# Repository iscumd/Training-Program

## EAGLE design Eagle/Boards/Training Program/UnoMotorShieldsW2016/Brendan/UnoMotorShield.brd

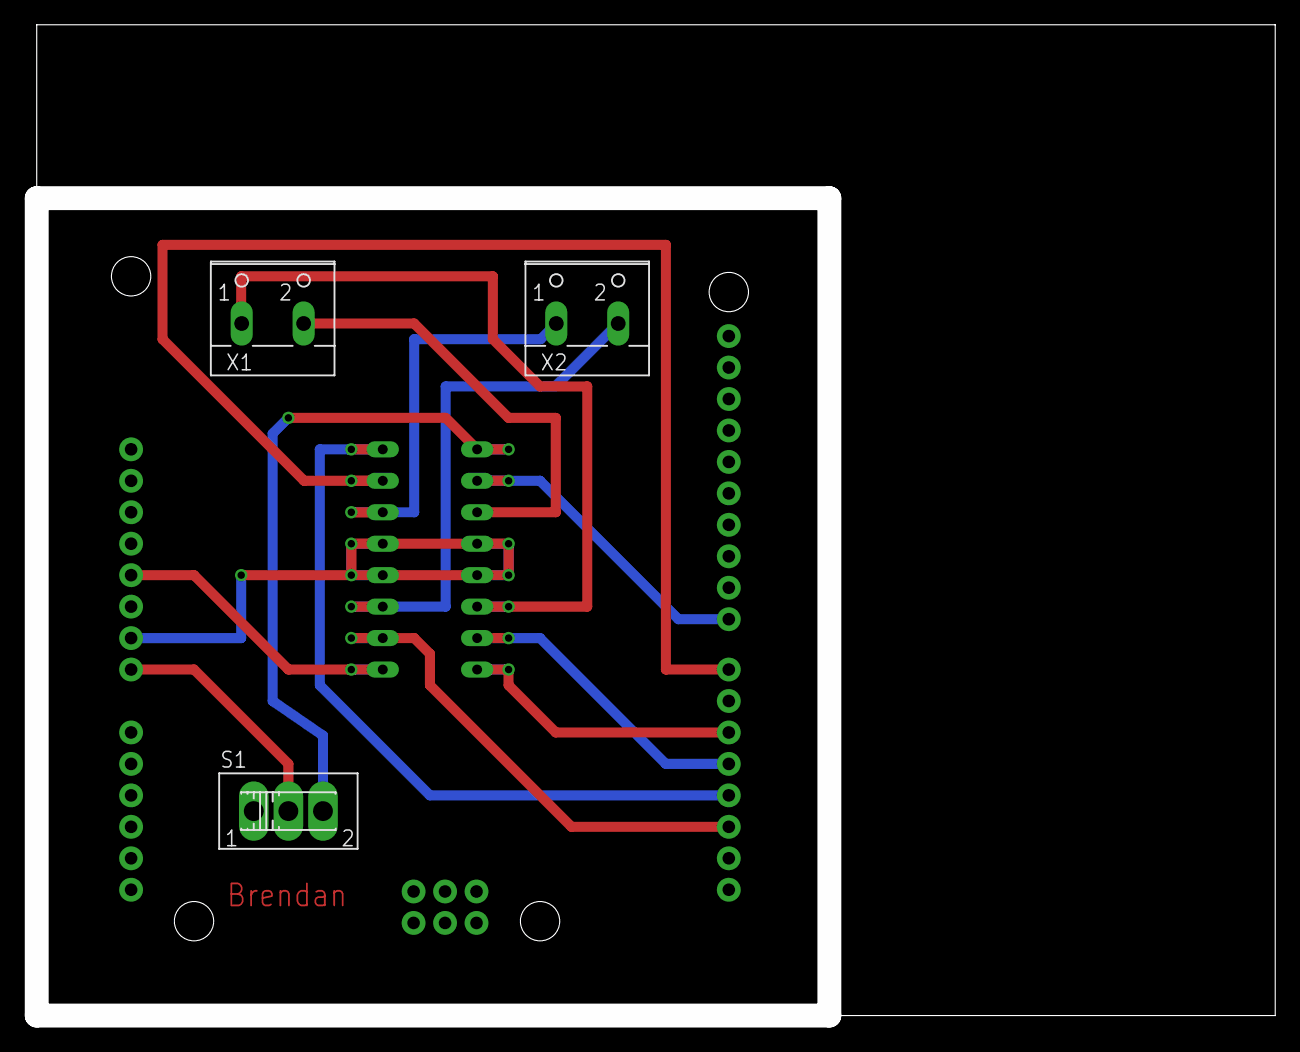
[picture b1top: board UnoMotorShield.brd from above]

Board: 2 copper layers, 100.0 x 80.0 mm, 5 parts (0 on the bottom side), 14 nets.

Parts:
J1: ARDUINO_UNO_R3; ARDUINO_R3
S1: SLIDE_SWITCH
U$1: MOTOR_DRIVERDIP16; DIP16
X1, X2: 2PIN-SCREW-TERMINAL

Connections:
unnamed: U$1.P3, X1.1
unnamed: U$1.P6, X1.2
unnamed: U$1.P11, X2.1
unnamed: U$1.P14, X2.2
unnamed: J1.5V, U$1.P16
unnamed: J1.GND@2, U$1.P4, U$1.P5, U$1.P12, U$1.P13
unnamed: J1.VIN, S1.2
unnamed: S1.3, U$1.P8
unnamed: J1.D2, U$1.P15
unnamed: J1.D3, U$1.P9
unnamed: J1.D4, U$1.P2
unnamed: J1.D5, U$1.P1
unnamed: J1.D7, U$1.P10
unnamed: J1.D8, U$1.P7

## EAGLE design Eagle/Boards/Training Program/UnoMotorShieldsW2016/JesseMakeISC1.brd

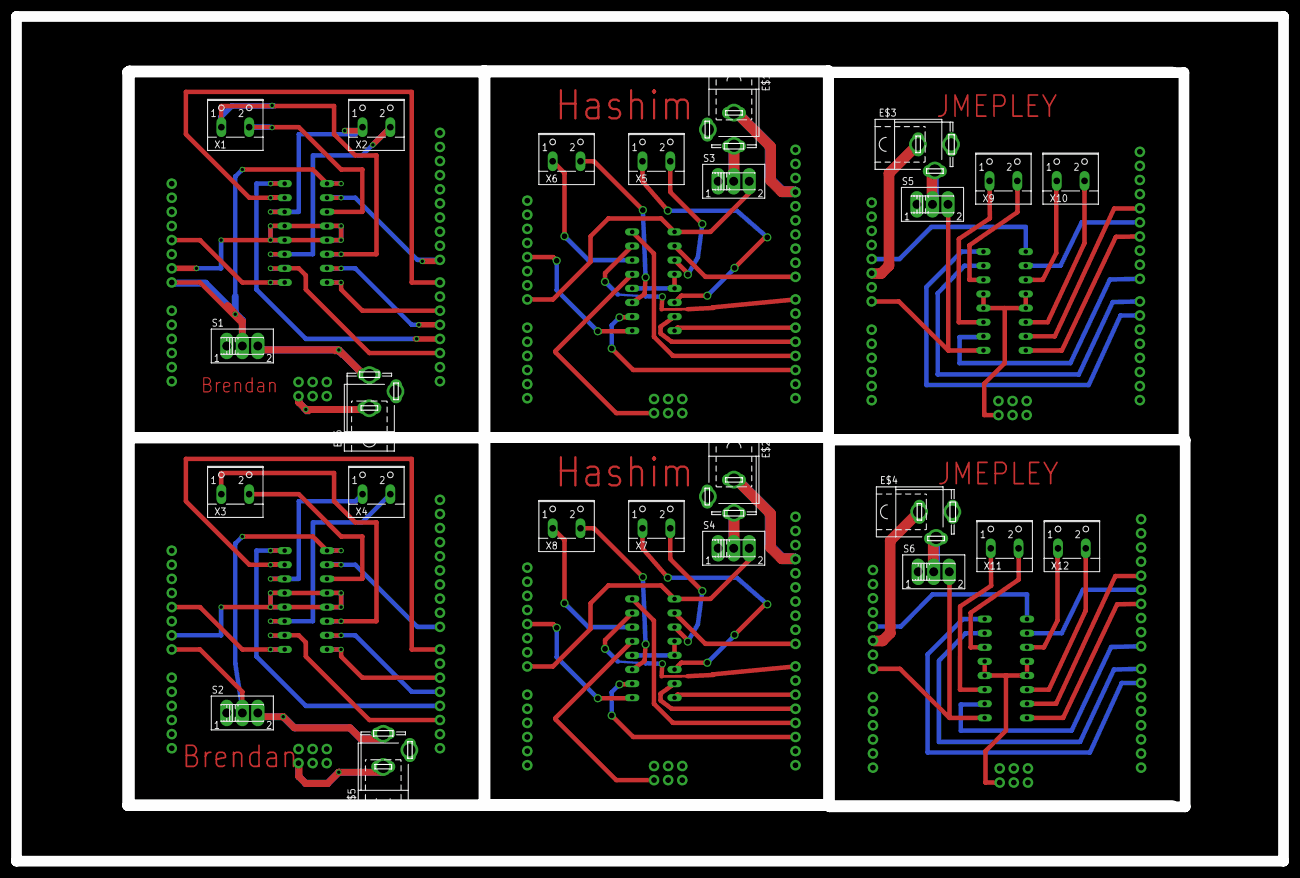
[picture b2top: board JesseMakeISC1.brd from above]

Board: 2 copper layers, 228.0 x 152.0 mm, 36 parts (0 on the bottom side), 80 nets.

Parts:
E$1, E$2, E$3, E$4, E$5, E$6: 5.5-2.5-BARRELCONNECTOR
J1, J2, J3, J4, J5, J6: ARDUINO_UNO_R3; ARDUINO_R3
S1, S2, S3, S4, S5, S6: SLIDE_SWITCH
U$1, U$2, U$3, U$4, U$5, U$6: MOTOR_DRIVERDIP16; DIP16
X1, X2, X3, X4, X5, X6, X7, X8, X9, X10, X11, X12: 2PIN-SCREW-TERMINAL

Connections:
1A: J5.D7, U$5.P2
1A1: J6.D7, U$6.P2
2A: J5.D8, U$5.P7
2A1: J6.D8, U$6.P7
3A: J5.D13, U$5.P10
3A1: J6.D13, U$6.P10
4A: J5.D12, U$5.P15
4A1: J6.D12, U$6.P15
EN1: J5.D6, U$5.P1
EN2: J5.D11, U$5.P9
EN3: J6.D11, U$6.P9
EN4: J6.D6, U$6.P1
GND: U$3.P4, U$3.P5, U$3.P13
GND1: U$4.P4, U$4.P5, U$4.P13
GND2: J5.GND@4, U$5.P4, U$5.P5, U$5.P12, U$5.P13
GND3: J6.GND@4, U$6.P4, U$6.P5, U$6.P12, U$6.P13
unnamed: U$1.P3, X1.1
unnamed: U$1.P6, X1.2
unnamed: U$1.P11, X2.1
unnamed: U$1.P14, X2.2
unnamed: J1.5V, U$1.P16
unnamed: J1.GND@2, U$1.P4, U$1.P5, U$1.P12, U$1.P13
unnamed: J1.VIN, S1.2, U$1.P8
unnamed: J1.D2, U$1.P15
unnamed: J1.D3, U$1.P9
unnamed: J1.D4, U$1.P2
unnamed: J1.D5, U$1.P1
unnamed: J1.D7, U$1.P10
unnamed: J1.D8, U$1.P7
unnamed: U$2.P3, X3.1
unnamed: U$2.P6, X3.2
unnamed: U$2.P11, X4.1
unnamed: U$2.P14, X4.2
unnamed: J2.5V, U$2.P16
unnamed: J2.GND@2, U$2.P4, U$2.P5, U$2.P12, U$2.P13
unnamed: J2.VIN, S2.2
unnamed: J2.D2, U$2.P15
unnamed: J2.D3, U$2.P9
unnamed: J2.D4, U$2.P2
unnamed: J2.D5, U$2.P1
unnamed: J2.D7, U$2.P10
unnamed: J2.D8, U$2.P7
unnamed: U$3.P3, X5.1
unnamed: U$3.P6, X5.2
unnamed: U$3.P11, X6.1
unnamed: U$3.P14, X6.2
unnamed: J3.5V, U$3.P16
unnamed: J3.GND@4, U$3.P12
unnamed: J3.VIN, S3.3, U$3.P8
unnamed: J3.D2, U$3.P15
unnamed: J3.D3, U$3.P9
unnamed: J3.D8, U$3.P7
unnamed: J3.D7, U$3.P10
unnamed: J3.D4, U$3.P2
unnamed: J3.D5, U$3.P1
unnamed: U$4.P3, X7.1
unnamed: U$4.P6, X7.2
unnamed: U$4.P11, X8.1
unnamed: U$4.P14, X8.2
unnamed: J4.5V, U$4.P16
unnamed: J4.GND@4, U$4.P12
unnamed: J4.VIN, S4.3, U$4.P8
unnamed: J4.D2, U$4.P15
unnamed: J4.D3, U$4.P9
unnamed: J4.D8, U$4.P7
unnamed: J4.D7, U$4.P10
unnamed: J4.D4, U$4.P2
unnamed: J4.D5, U$4.P1
unnamed: U$5.P6, X9.1
unnamed: U$5.P3, X9.2
unnamed: U$5.P14, X10.1
unnamed: U$5.P11, X10.2
unnamed: J5.5V, U$5.P16
unnamed: J5.VIN, S5.3, U$5.P8
unnamed: U$6.P6, X11.1
unnamed: U$6.P3, X11.2
unnamed: U$6.P14, X12.1
unnamed: U$6.P11, X12.2
unnamed: J6.5V, U$6.P16
unnamed: J6.VIN, S6.3, U$6.P8

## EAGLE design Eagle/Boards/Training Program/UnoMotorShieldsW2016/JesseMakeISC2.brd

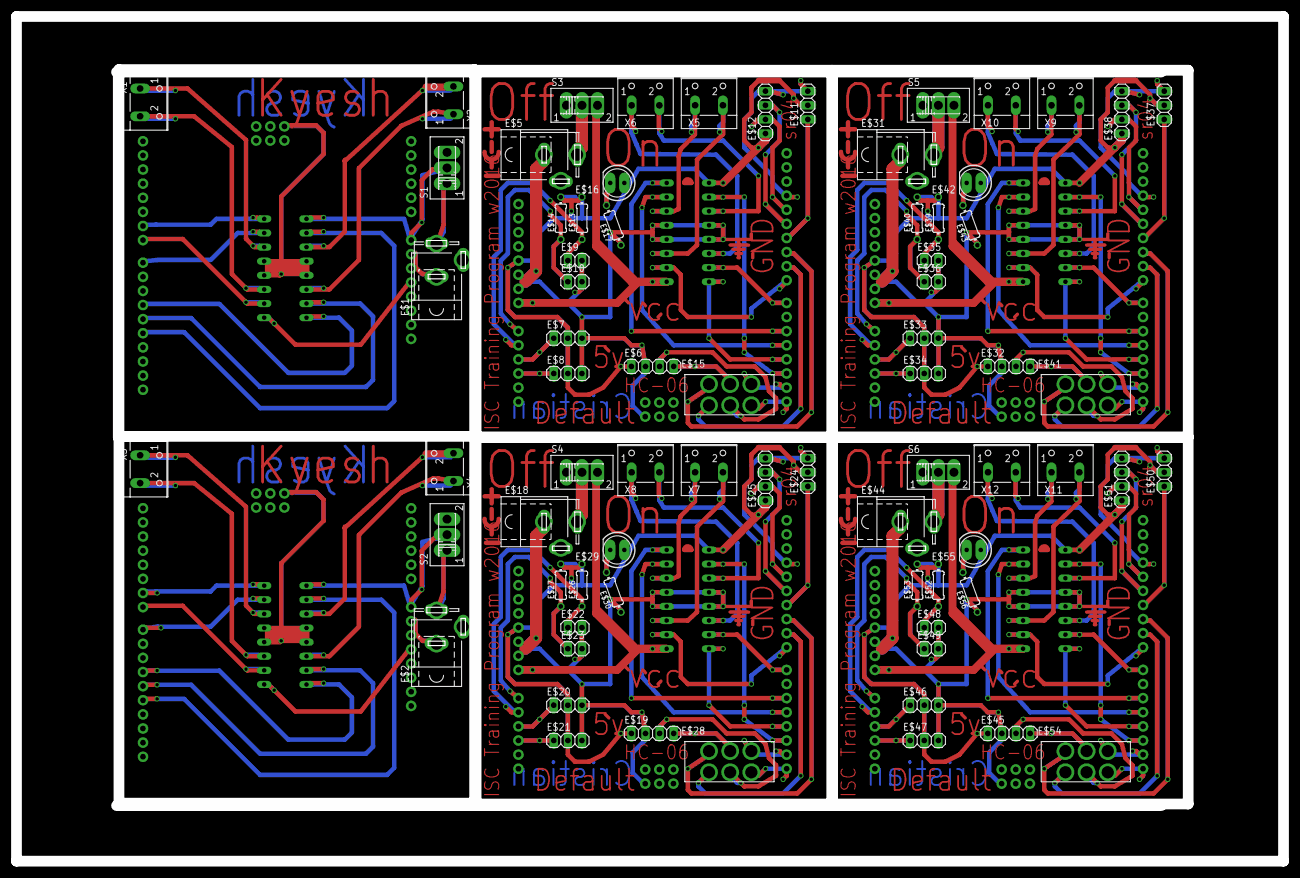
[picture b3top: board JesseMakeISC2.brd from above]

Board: 2 copper layers, 228.0 x 152.0 mm, 84 parts (0 on the bottom side), 78 nets.

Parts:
E$1, E$2, E$5, E$18, E$31, E$44: 5.5-2.5-BARRELCONNECTOR
E$3, E$4: ARDUINO_R3
E$6, E$12, E$19, E$25, E$32, E$38, E$45, E$51: 1X04
E$7, E$8, E$11, E$20, E$21, E$24, E$33, E$34, E$37, E$46, E$47, E$50: 1X03
E$9, E$10, E$22, E$23, E$35, E$36, E$48, E$49: 1X02
E$13, E$14, E$17, E$26, E$27, E$30, E$39, E$40, E$43, E$52, E$53, E$56: 0204/7
E$15, E$28, E$41, E$54: DUAL_SLIDE_SWITCH
E$16, E$29, E$42, E$55: LED5MM
ENABLE, ENABLE1: MOTOR_DRIVERDIP16; DIP16
J1, J2, J3, J4: ARDUINO_UNO_R3; ARDUINO_R3
S1, S2, S3, S4, S5, S6: SLIDE_SWITCH
U$1, U$2, U$3, U$4: MOTOR_DRIVERDIP16; DIP16
X1, X2, X3, X4, X5, X6, X7, X8, X9, X10, X11, X12: 2PIN-SCREW-TERMINAL

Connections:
GND: ENABLE.P4, ENABLE.P5, ENABLE.P12
GND1: ENABLE1.P4, ENABLE1.P5, ENABLE1.P12
unnamed: ENABLE.P3, X2.1
unnamed: ENABLE.P8, S1.2
unnamed: ENABLE.P11, X1.1
unnamed: ENABLE.P14, X1.2
unnamed: ENABLE1.P3, X4.1
unnamed: ENABLE1.P8, S2.2
unnamed: ENABLE1.P11, X3.1
unnamed: ENABLE1.P14, X3.2
unnamed: U$1.P6, X5.2
unnamed: U$1.P14, X6.2
unnamed: U$1.P11, X6.1
unnamed: E$6.1, E$8.2, E$12.1, E$13.2, E$14.2, J1.5V, U$1.P16
unnamed: E$6.2, E$8.3, E$9.2, U$1.P4, U$1.P5, U$1.P12, U$1.P13
unnamed: J1.VIN, S3.3, U$1.P8
unnamed: J1.D2, U$1.P15
unnamed: J1.D3, U$1.P9
unnamed: J1.D7, U$1.P10
unnamed: J1.D5, U$1.P1
unnamed: J1.D4, U$1.P2
unnamed: U$1.P3, X5.1
unnamed: J1.D8, U$1.P7
unnamed: U$2.P6, X7.2
unnamed: U$2.P14, X8.2
unnamed: U$2.P11, X8.1
unnamed: E$19.1, E$21.2, E$25.1, E$26.2, E$27.2, J2.5V, U$2.P16
unnamed: E$19.2, E$21.3, E$22.2, U$2.P4, U$2.P5, U$2.P12, U$2.P13
unnamed: J2.VIN, S4.3, U$2.P8
unnamed: J2.D2, U$2.P15
unnamed: J2.D3, U$2.P9
unnamed: J2.D7, U$2.P10
unnamed: J2.D5, U$2.P1
unnamed: J2.D4, U$2.P2
unnamed: U$2.P3, X7.1
unnamed: J2.D8, U$2.P7
unnamed: U$3.P6, X9.2
unnamed: U$3.P14, X10.2
unnamed: U$3.P11, X10.1
unnamed: E$32.1, E$34.2, E$38.1, E$39.2, E$40.2, J3.5V, U$3.P16
unnamed: E$32.2, E$34.3, E$35.2, U$3.P4, U$3.P5, U$3.P12, U$3.P13
unnamed: J3.VIN, S5.3, U$3.P8
unnamed: J3.D2, U$3.P15
unnamed: J3.D3, U$3.P9
unnamed: J3.D7, U$3.P10
unnamed: J3.D5, U$3.P1
unnamed: J3.D4, U$3.P2
unnamed: U$3.P3, X9.1
unnamed: J3.D8, U$3.P7
unnamed: U$4.P6, X11.2
unnamed: U$4.P14, X12.2
unnamed: U$4.P11, X12.1
unnamed: E$45.1, E$47.2, E$51.1, E$52.2, E$53.2, J4.5V, U$4.P16
unnamed: E$45.2, E$47.3, E$48.2, U$4.P4, U$4.P5, U$4.P12, U$4.P13
unnamed: J4.VIN, S6.3, U$4.P8
unnamed: J4.D2, U$4.P15
unnamed: J4.D3, U$4.P9
unnamed: J4.D7, U$4.P10
unnamed: J4.D5, U$4.P1
unnamed: J4.D4, U$4.P2
unnamed: U$4.P3, X11.1
unnamed: J4.D8, U$4.P7
S$27: E$11.3, E$12.4
S$34: E$10.1, E$14.1, J1.A0
S$36: E$7.1, J1.A2
S$37: E$8.1, J1.A3
S$73: E$24.3, E$25.4
S$80: E$23.1, E$27.1, J2.A0
S$82: E$20.1, J2.A2
S$83: E$21.1, J2.A3
S$119: E$37.3, E$38.4
S$126: E$36.1, E$40.1, J3.A0
S$128: E$33.1, J3.A2
S$129: E$34.1, J3.A3
S$165: E$50.3, E$51.4
S$172: E$49.1, E$53.1, J4.A0
S$174: E$46.1, J4.A2
S$175: E$47.1, J4.A3

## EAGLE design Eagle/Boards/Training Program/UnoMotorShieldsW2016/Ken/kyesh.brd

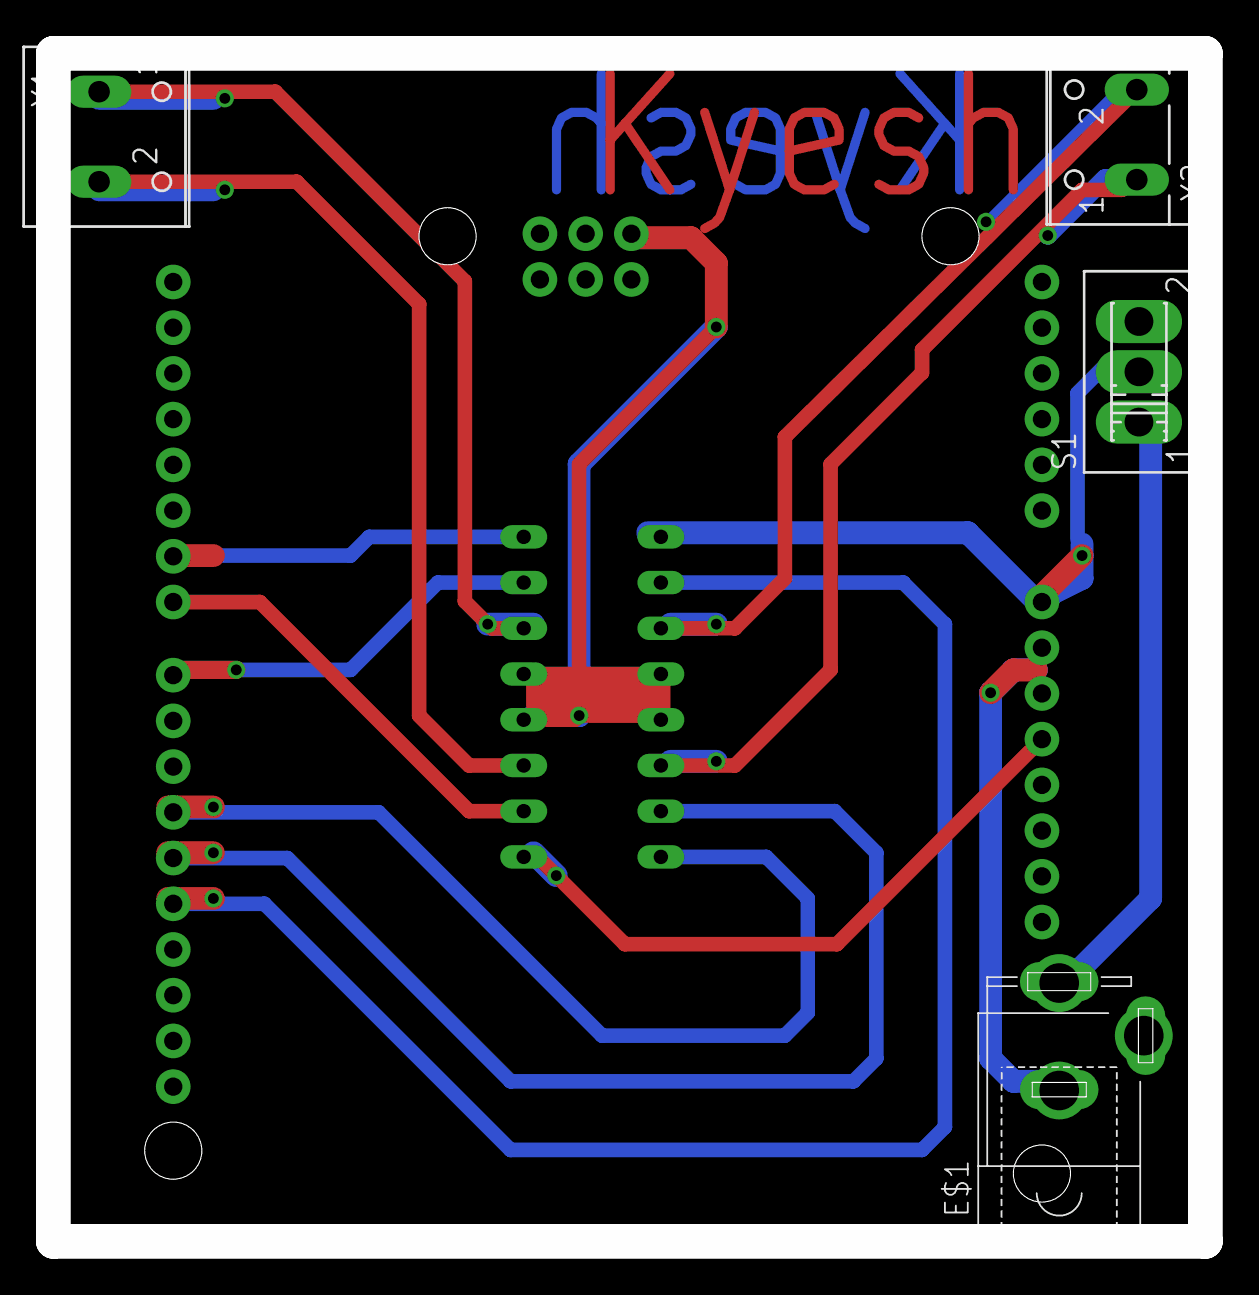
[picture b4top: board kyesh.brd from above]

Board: 2 copper layers, 64.0 x 66.0 mm, 6 parts (0 on the bottom side), 14 nets.

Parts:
E$1: 5.5-2.5-BARRELCONNECTOR
ENABLE: MOTOR_DRIVERDIP16; DIP16
J1: ARDUINO_UNO_R3; ARDUINO_R3
S1: SLIDE_SWITCH
X1, X2: 2PIN-SCREW-TERMINAL

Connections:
ENABLE: ENABLE.P1, J1.D11
GND: ENABLE.P4, ENABLE.P5, ENABLE.P12
unnamed: ENABLE.P3, X2.1
unnamed: ENABLE.P13, J1.GND@4
unnamed: ENABLE.P16, J1.5V
unnamed: ENABLE.P8, J1.VIN
unnamed: ENABLE.P6, X2.2
unnamed: ENABLE.P11, X1.1
unnamed: ENABLE.P14, X1.2
unnamed: ENABLE.P10, J1.D8
unnamed: ENABLE.P2, J1.D12
unnamed: ENABLE.P7, J1.D13
unnamed: ENABLE.P9, J1.D6
unnamed: ENABLE.P15, J1.D7
